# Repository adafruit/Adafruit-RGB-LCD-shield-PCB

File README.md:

# RGB LCD Shield Kit

This new Adafruit shield makes it easy to use a 16x2 Character LCD. We really like the RGB LCDs we stock in the shop both the [RGB negative](http://www.adafruit.com/products/399) and [RGB positive](http://www.adafruit.com/products/398). Unfortunately, these LCDs do require quite a few digital pins, 6 to control the LCD and then another 3 to control the RGB backlight for a total of 9 pins. That's half of the pins available on a classic Arduino!

With this in mind, we wanted to make it easier for people to get these LCD into their projects so we devised a shield that lets you control __a 16x2 Character LCD, up to 3 backlight pins AND 5 keypad pins using only the two I2C pins on the Arduino!__ The best part is you don't really lose those two pins either, since you can stick i2c-based sensors, RTCs, etc and have them share the I2C bus. This is a super slick way to add a display without all the wiring hassle.

This shield is perfect for when you want to build a stand-alone project with its own user interface. The 4 directional buttons plus select button allows basic control without having to attach a bulky computer.

The shield is designed for 'classic' Arduinos such as the Uno, Duemilanove, Diecimilla, etc. It uses the I2C pins at Analog 4 and Analog 5. It will also work perfectly with Arduino Mega R3's which have the extra SDA/SCL I2C pins broken out. Earlier Mega's have the I2C pins in a different location and will require you to solder two wires from the I2C pins on the shield and plug them into the different I2C locations at Digital 20 & 21. This shield will not fit easily on top of an Arduino Ethernet because of the Ethernet jack height. [You can use a set of stacking headers to give the shield more 'lift' above the jack](http://www.adafruit.com/products/85).

__This product comes as a kit!__ Included is a high quality, USA-made PCB and all the components (buttons, header etc). This product comes with a [16x2 RGB negative](http://www.adafruit.com/products/399). Assembly is easy, even if you've never soldered before and the kit can be completed in 30 minutes. [Check the product tutorial page for assembly instructions before purchasing](http://learn.adafruit.com/rgb-lcd-shield).

### License

Adafruit invests time and resources providing this open source design, please support Adafruit and open-source hardware by purchasing products from [Adafruit](https://www.adafruit.com)!

Designed by Limor Fried/Ladyada for Adafruit Industries.

Creative Commons Attribution/Share-Alike, all text above must be included in any redistribution. See license.txt for additional details.

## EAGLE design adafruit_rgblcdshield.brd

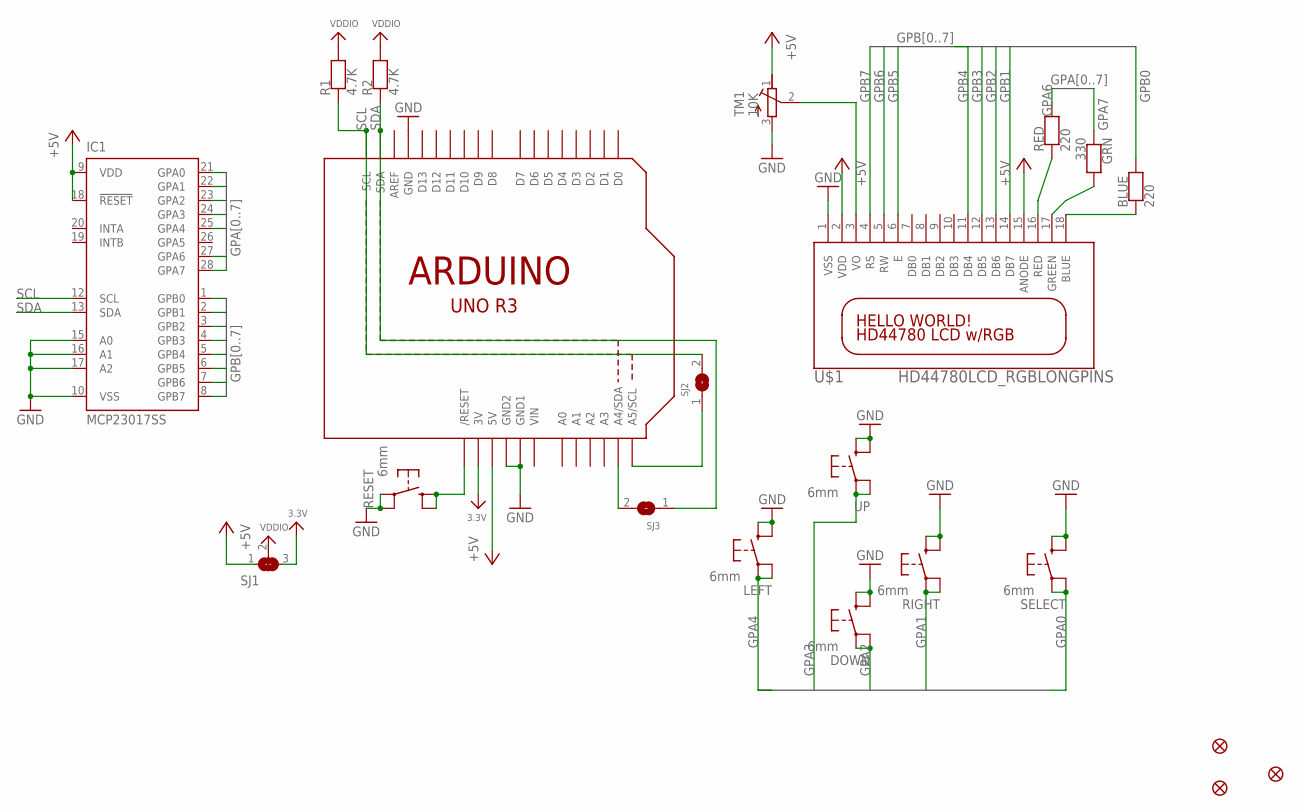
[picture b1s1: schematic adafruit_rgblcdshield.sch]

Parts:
BLUE: 220; 0805-NO
DOWN: 6mm; 6MMX6MM_TACTILE_SMT
FID1, FID2, FID3: FIDUCIAL_1MM
GRN: 330; 0805-NO
IC1: MCP23017SS; SSOP28
LEFT: 6mm; 6MMX6MM_TACTILE_SMT
R1, R2: 4.7K; 0805-NO
RED: 220; 0805-NO
RESET: 6mm; 6MMX6MM_TACTILE_SMT
RIGHT: 6mm; 6MMX6MM_TACTILE_SMT
SELECT: 6mm; 6MMX6MM_TACTILE_SMT
SJ1: SOLDERJUMPER_2WAY; SOLDERJUMPER_2WAY_OPEN_NOPASTE
SJ2, SJ3: SOLDERJUMPER; SOLDERJUMPER_ARROW_NOPASTE
TM1: 10K; RTRIM3314J
U1: ARDUINOR3-NOIOREF-NOTEXT; ARDUINOR3-NOTEXT-NOIOREF
U$1: HD44780LCD_RGBLONGPINS; LCD1602-RGB
UP: 6mm; 6MMX6MM_TACTILE_SMT

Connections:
3.3V: SJ1.3, U1.3V
+5V: IC1.9 (VDD), IC1.18 (!RESET), SJ1.1, TM1.1 (E), U1.5V, U$1.2 (VDD), U$1.15 (ANODE)
GND: DOWN.B (S), DOWN.B' (S1), IC1.10 (VSS), IC1.15 (A0), IC1.16 (A1), IC1.17 (A2), LEFT.B (S), LEFT.B' (S1), RESET.A, RESET.A' (P1), RIGHT.B (S), RIGHT.B' (S1), SELECT.B (S), SELECT.B' (S1), TM1.3 (A), U1.GND, U1.GND1, U1.GND2, U$1.1 (VSS), UP.B (S), UP.B' (S1)
GPA0: IC1.21 (GPA0), SELECT.A, SELECT.A' (P1)
GPA1: IC1.22 (GPA1), RIGHT.A, RIGHT.A' (P1)
GPA2: DOWN.A, DOWN.A' (P1), IC1.23 (GPA2)
GPA3: IC1.24 (GPA3), UP.A, UP.A' (P1)
GPA4: IC1.25 (GPA4), LEFT.A, LEFT.A' (P1)
GPA6: IC1.27 (GPA6), RED.2
GPA7: GRN.1, IC1.28 (GPA7)
GPB0: BLUE.2, IC1.1 (GPB0)
GPB1: IC1.2 (GPB1), U$1.14 (DB7)
GPB2: IC1.3 (GPB2), U$1.13 (DB6)
GPB3: IC1.4 (GPB3), U$1.12 (DB5)
GPB4: IC1.5 (GPB4), U$1.11 (DB4)
GPB5: IC1.6 (GPB5), U$1.6 (E)
GPB6: IC1.7 (GPB6), U$1.5 (RW)
GPB7: IC1.8 (GPB7), U$1.4 (RS)
unnamed: BLUE.1, U$1.18 (BLUE)
unnamed: GRN.2, U$1.17 (GREEN)
unnamed: RED.1, U$1.16 (RED)
unnamed: TM1.2 (S), U$1.3 (VO)
unnamed: SJ3.2, U1.A4 (A4/SDA)
unnamed: SJ2.1, U1.A5 (A5/SCL)
RESET: RESET.B (S), RESET.B' (S1), U1.RESET (/RESET)
SCL: IC1.12 (SCL), R1.1, SJ2.2, U1.SCL
SDA: IC1.13 (SDA), R2.1, SJ3.1, U1.SDA
VDDIO: R1.2, R2.2, SJ1.2
VIN: U1.VIN

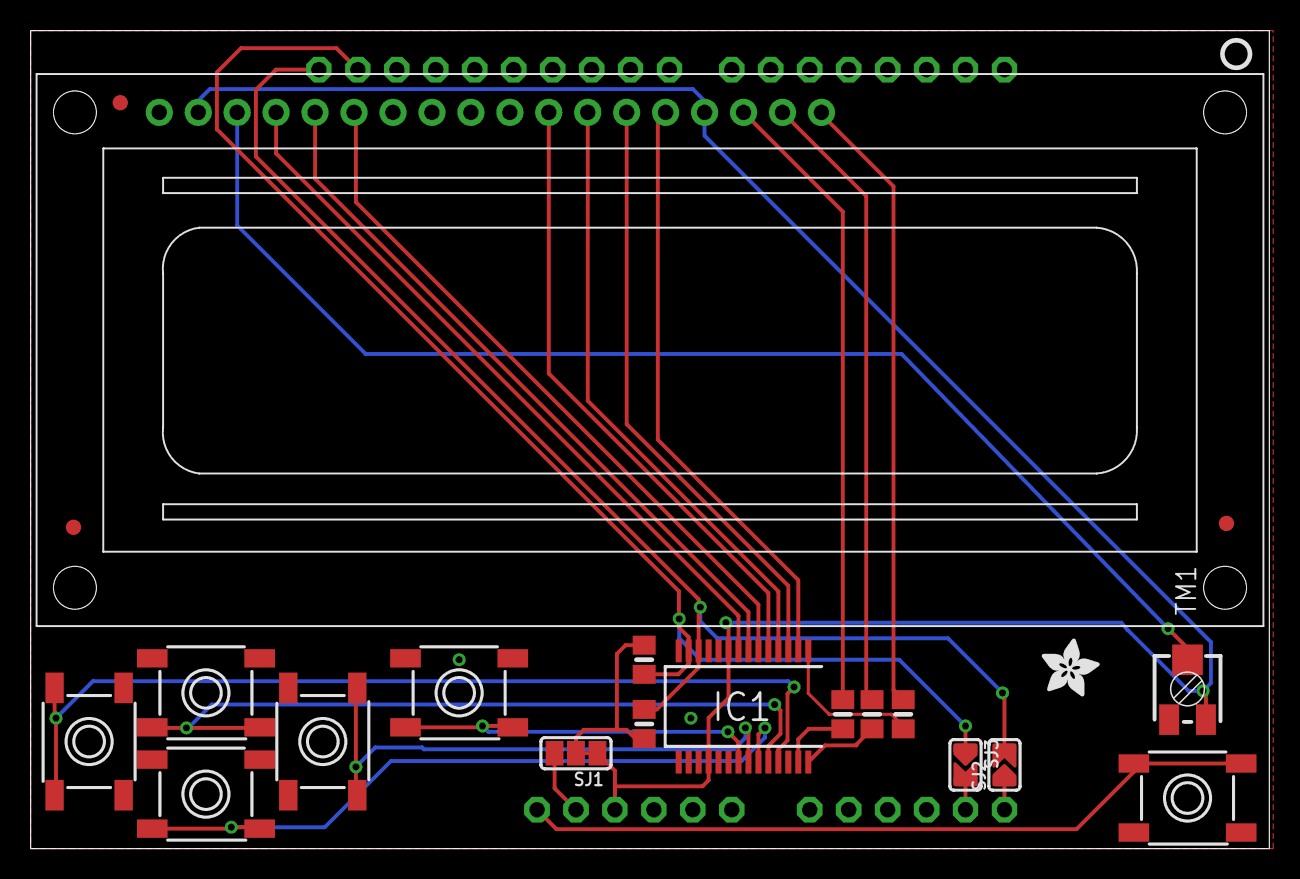
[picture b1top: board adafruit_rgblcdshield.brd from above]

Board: 2 copper layers, 80.8 x 53.3 mm, 38 parts (0 on the bottom side), 28 nets.

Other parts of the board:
E$1: PCBFEAT-REV-040
PLABEL1: PLABEL1
PLABEL2: PLABEL2
PLABEL3: PLABEL3
PLABEL4: PLABEL4
PLABEL5: PLABEL5
PLABEL6: PLABEL6
PLABEL7: PLABEL7
PLABEL8: PLABEL8
PLABEL9: PLABEL9
PLABEL10: PLABEL10
PLABEL11: PLABEL11
PLABEL12: PLABEL12
PLABEL13: PLABEL13
PLABEL14: PLABEL14
PLABEL15: PLABEL15
U$4: ADAFRUIT_3.5MM

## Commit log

2011-12-25 layed out, lets make it!
2011-12-25 shifted chip to the right
2012-02-15 silk tweaks
2012-02-15 skootched the schematic
2012-02-15 rename!
2019-03-28 image + readme
2024-03-14 Update Schematic and board
2024-06-04 adding rev B files
